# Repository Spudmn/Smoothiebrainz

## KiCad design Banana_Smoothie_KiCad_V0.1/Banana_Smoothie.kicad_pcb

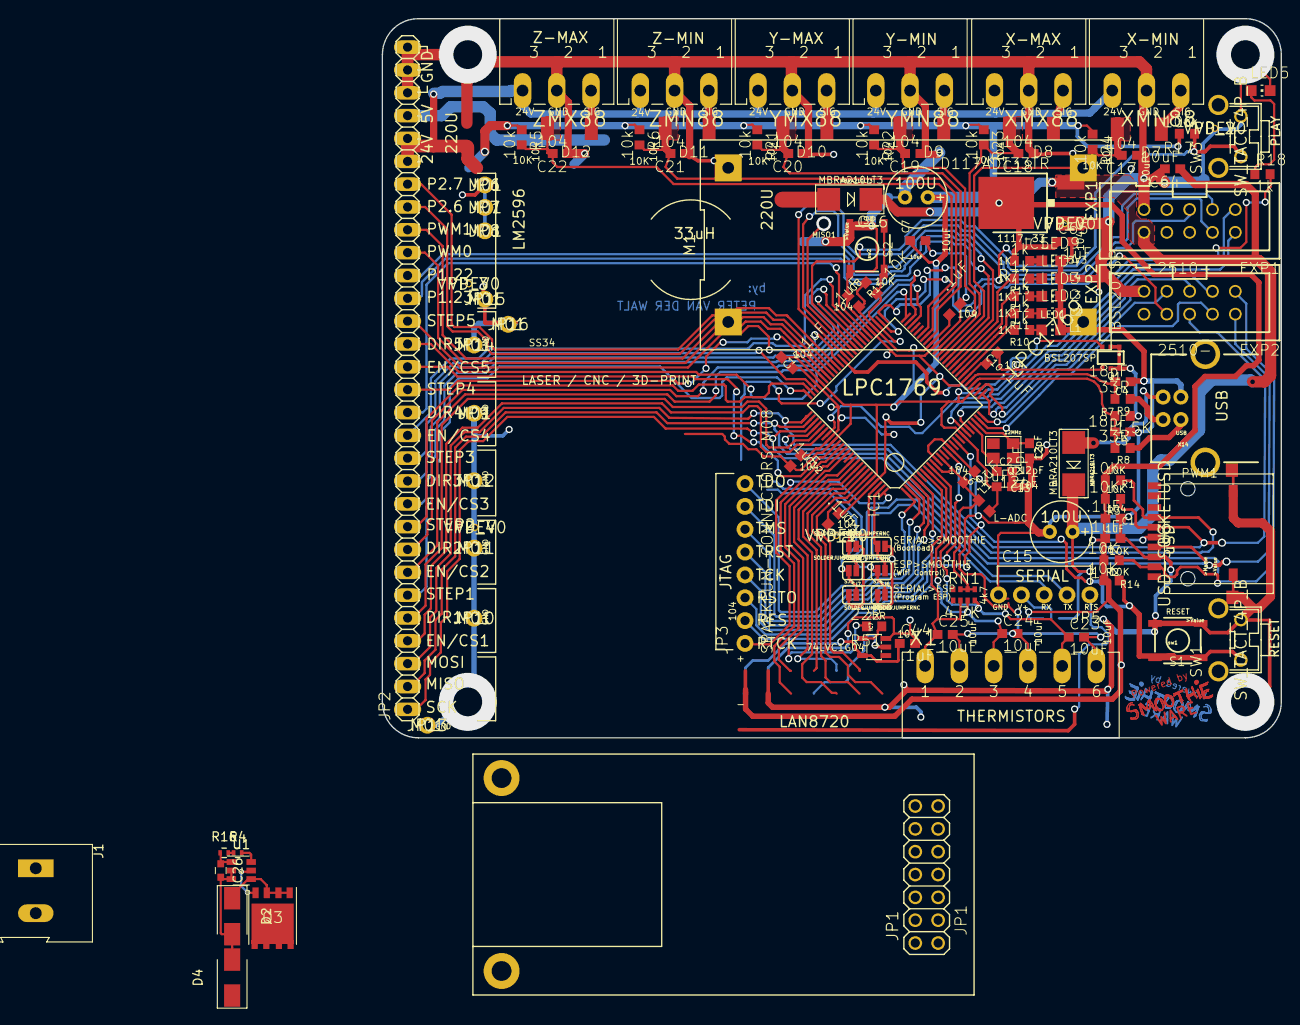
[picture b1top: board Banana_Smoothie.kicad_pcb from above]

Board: 2 copper layers, 100.0 x 80.0 mm, 124 parts (0 on the bottom side), 104 nets.

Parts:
C1, C6, C8, C9, C10, C11, C12, C13, C14, C44, C65: .1uF; C0603
C2, C3: 12pF; C0603
C4, C5: 18pF; C0603
C7, C23, C24, C25, C64: 10uF; C0603
C15, C16: E2,5-7
C17, C18, C19, C20, C21, C22: 104; C0603
C26: 100n; C_0603
C67: 1uF; C0603
D1, D3: MBRA210LT3; SMADIODE
D2, D4: SS16; D_SMA_Standard
D7, D8, D9, D10, D11, D12: SOD87
EXP1, EXP2: 2510-; PAK100%2f2500-10
IC1: LPC1769; LQFP100
IC5: LD117ADT33TR; DPACK
IC7: SOT23-5
J1: Screw_Terminal_1x02; AK300-2
JP1: JP1; LAN8720_Module
JP2: 1X30
JP3: SPARKFUN-CONNECTORS_M08; 1X08_NO_SILK
JP5: 1; 1X05_NO_SILK
JP6, JP7, JP8, JP9, JP10, JP11, JP12, JP13, JP14, JP15, JP16: M01; 1X01NS-KIT
L1: 0603
LED1, LED2, LED3, LED4, LED5, LED9: CHIP-LED0805
M1: LM2596_Module
NT1: Net Tie; NET-TIE-0.3mm
Q1: BSL207SP; SC74_INFINEON
Q2: 12MHz; CRYSTAL_3.2X2.5
Q3: Q_NMOS_DSG; PG-TDSON-8
R1, R2, R3, R14, R15, R17: 10K; R0603
R4, R16: 47R; R_0402
R5, R6, R21, R22, R23, R24: 10k; R0603
R7: 1.5K; R0603
R8, R9: 33R; R0603
R10, R11, R12, R13, R18, R77: 1k; R0603
R51: 22R; R0603
RN1: 4.7K; 0603-ARV
S1: sw1; TACTILE_SWITCH_SMD
S2: sw2; TACTILE_SWITCH_SMD
SJ1: 1; SJ_3
SJ2, SJ3, SJ4, SJ5, SJ6, SJ7: SOLDERJUMPERNC; SJ_2S
SW1, SW3: SW_TACT_4P_B; SW_TACT_STANDARD_RIGHT_ANGLE
U1: LM5050; SOT-23-6
U3: USD-SOCKETUSD; USD-SOCKET-PP
VP_0, VP_1, VP_2, VP_3, VP_4: VPDEV0; VPAC0
X1: MC1.5%2f6-G-3.81
X14: USB; SPARKFUN_USB-B-PTH
XMN88: MC1.5%2f3-G-3.81
XMX88: MC1.5%2f3-G-3.81
YMN88: MC1.5%2f3-G-3.81
YMX88: MC1.5%2f3-G-3.81
ZMN88: MC1.5%2f3-G-3.81
ZMX88: MC1.5%2f3-G-3.81

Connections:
5V: C15.+, C64.1, D1.C, D3.C, EXP1.10, IC5.3, SJ1.3
5vreg: D3.A, JP2.27, M1.OUT+
+3V3: C1.2, C7.1, C8.2, C9.2, C10.2, C11.2, C12.2, C13.2, C14.2, C16.+, C44.1, C65.1, C67.2, IC1.19, IC1.28, IC1.42, IC1.54, IC1.71, IC1.84, IC1.96, IC5.4, IC7.5, JP1.1, JP1.2, L1.2, Q1.4, R1.2, R2.2, R3.2, R5.1, R6.1, R14.2, R15.2, R17.2, R21.1, R22.1, R23.1, R24.1, R77.2, SJ1.1, U3.4
/24V: JP2.25, JP2.26, M1.IN+, Q3.D, R4.2, U1.6, XMN88.3, XMX88.3, YMN88.3, YMX88.3, ZMN88.3, ZMX88.3
/AVCC: C6.1, IC1.10, IC1.12, L1.1, RN1.1, RN1.2, RN1.3
/BUZZER-RRD: EXP1.1, IC1.20
/DIR1: IC1.80, JP2.5
/DIR2: IC1.49, JP2.8
/DIR3: IC1.58, JP2.11
/DIR4: IC1.56, JP2.14
/DIR5: IC1.50, JP2.17
/EN1: IC1.81, JP2.4
/EN2: IC1.48, JP2.7
/EN3: IC1.59, JP2.10
/EN4: IC1.57, JP2.13
/EN5: IC1.85, JP2.16
/ENET_CRS: IC1.92, JP1.7
/ENET_MDC: IC1.87, JP1.5
/ENET_MDIO: IC1.86, JP1.6
/ENET_REF_CLK: IC1.88, R51.2
/ENET_RXD0: IC1.91, JP1.10
/ENET_RXD1: IC1.90, JP1.9
/ENET_TXD0: IC1.95, JP1.11
/ENET_TXD1: IC1.94, JP1.14
/ENET_TX_EN: IC1.93, JP1.12
/ESPRX: SJ5.2, SJ7.2
/ESPTX: SJ4.2, SJ6.2
/ISP_BOOT: IC1.53, R15.1
/JTAG-RTCK: IC1.100, JP3.1
/JTAG-TCK: IC1.5, JP3.4
/JTAG-TDI: IC1.2, JP3.7
/JTAG-TDO: IC1.1, JP3.8
/JTAG-TMS: IC1.3, JP3.6
/JTAG-TRST: IC1.4, JP3.5
/LED1: IC1.32, R10.2
/LED2: IC1.33, R11.2
/LED3: IC1.34, R12.2
/LED4: IC1.35, R13.2
/MOSI1: EXP1.3, IC1.60
/N$1: C2.1, IC1.22, Q2.2
/N$2: C3.1, IC1.23, Q2.1
/N$6: D7.1, XMN88.1
/N$8: D8.1, XMX88.1
/N$10: D9.1, YMN88.1
/N$12: D10.1, YMX88.1
/N$15: D11.1, ZMN88.1
/N$16: D12.1, ZMX88.1
/N$23: JP5.4, SJ1.2
/N$51: Q1.1, Q1.2, Q1.5, Q1.6, R7.2
/N$61: R8.1, X14.D+
/N$62: R9.1, X14.D-
/N$77: IC7.2, JP1.8
/N$78: IC7.4, R51.1
/P1_22-3RD-SMALL-FET: IC1.36, JP2.20
/P1_23-3RD-LARGE-FET: IC1.37, JP2.19
/P1_30_CLICK-ON-RRD: EXP1.2, IC1.21
/P2.6_FAN_FET: IC1.67, JP2.23
/P2.7_HOTEND_FET: IC1.66, JP2.24
/P2.9: IC1.64, Q1.3
/PLAY: IC1.51, R17.1, SW3.1
/PLAY_LED: IC1.82, R18.2
/PWM0_PSU_OUT: IC1.69, JP2.21
/PWM1_BED_HEATER: IC1.68, JP2.22
/RESET: IC1.17, JP3.2, R14.1, SW1.1
/RSTOUT: IC1.14, JP3.3
/RX_0: IC1.99, SJ2.2, SJ6.1
/RX_FT: JP5.3, SJ2.1, SJ4.1
/SCK1: EXP1.5, IC1.62
/SD-CD-ON-RRD: EXP2.7, IC1.25
/SD-CS-ON-RRD: EXP2.4, IC1.24
/SD_CD/KILL-ON-RRD: EXP2.8, IC1.52
/SD_CS: IC1.79, R1.1, U3.2
/SD_IRQ-ENC-A-ON-RRD: EXP2.5, IC1.27
/SD_MISO: EXP2.1, IC1.77, JP2.2, R2.1, U3.7
/SD_MOSI: EXP2.6, IC1.76, JP2.3, R3.1, U3.3
/SD_SCK: EXP2.2, IC1.78, JP2.1, U3.5
/SD_WP-ENC-B-ON-RRD: EXP2.3, IC1.26
/SSEL1: EXP1.4, IC1.63
/STP1: IC1.75, JP2.6
/STP2: IC1.74, JP2.9
/STP3: IC1.73, JP2.12
/STP4: IC1.70, JP2.15
/STP5: IC1.65, JP2.18
/TH1_HOTEND: C23.1, IC1.9, RN1.8, X1.5
/TH2_BED: C24.1, IC1.8, RN1.7, X1.3
/TH3: C25.1, IC1.7, RN1.6, X1.1
/TX_0: IC1.98, SJ3.2, SJ7.1
/TX_FT: JP5.2, SJ3.1, SJ5.1
/USB_D+: C5.2, IC1.29, R7.1, R8.2
/USB_D-: C4.2, IC1.30, R9.2
/X_MAX: C18.2, D8.2, IC1.39, R23.2
/X_MIN: C17.2, D7.2, IC1.38, R24.2
/Y_MAX: C20.2, D10.2, IC1.43, R21.2
/Y_MIN: C19.2, D9.2, IC1.40, R22.2
/Z_MAX: C22.2, D12.2, IC1.45, R5.2
/Z_MIN: C21.2, D11.2, IC1.44, R6.2
GND: C1.1, C2.2, C3.2, C4.1, C5.1, C7.2, C8.1, C9.1, C10.1, C11.1, C12.1, C13.1, C14.1, C15.-, C16.-, C17.1, C18.1, C19.1, C20.1, C21.1, C22.1, C44.2, C64.2, C65.2, C67.1, D4.1, EXP1.9, EXP2.9, IC1.31, IC1.41, IC1.55, IC1.72, IC1.83, IC1.97, IC5.1, IC7.3, J1.2, JP1.3, JP1.4, JP2.28, JP2.29, JP2.30, JP5.5, JP6.1, JP7.1, JP8.1, JP9.1, JP10.1, JP11.1, JP12.1, JP13.1, JP14.1, JP15.1, JP16.1, M1.IN-, M1.OUT-, NT1.2, SW1.2, SW3.2, U3.6, U3.CD1, U3.CD2, U3.GND1, VP_0.VP, VP_1.VP, VP_2.VP, VP_3.VP, VP_4.VP, X14.GND, XMN88.2, XMX88.2, YMN88.2, YMX88.2, ZMN88.2, ZMX88.2
GNDA: C6.2, C23.2, C24.2, C25.2, IC1.11, IC1.15, NT1.1, X1.2, X1.4, X1.6
unnamed: C26.1, R16.1, U1.1
unnamed: C26.2, D2.2, D4.2, U1.2, U1.3
unnamed: D2.1, J1.1, Q3.S, U1.4
unnamed: Q3.G, U1.5
unnamed: R4.1, R16.2
VUSB: D1.A, X14.VBUS

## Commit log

2016-12-15 Removed @1 from the c0603 Caps
2016-12-19 Added KiCad version of V0.2
2016-12-19 Moved Items on to page Started to fix up components
2016-12-19 Fixed Inductors and Caps and 3.3V and GND
2016-12-19 Fixed up more components The remaining components will be deleted soon
2017-01-09 More Clean up of Sch
2017-01-09 More Cleaning up
2017-01-10 More PCB Clean up Started to resize under size vias
2017-01-10 Via clean up
2017-01-10 More Via Clean up
2017-01-12 Changed one more Via
2017-01-12 Cleaned up logo
2017-01-17 Added Banana_Smoothie first commit
2017-01-19 Added LAN8720_Module
2017-01-22 Added reverse polarity protection
